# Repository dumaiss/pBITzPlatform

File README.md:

# pBITz Platform

pBITz is the shared hardware platform used by the **Coffee Series** of homebrew computers. It provides the common physical and electrical foundation — backplane, power control, service interfaces, reusable KiCad assets, test hardware, and platform tools — while leaving the personality of each machine to its CPU board and machine-specific peripherals.

The goal is not to define one rigid computer architecture. Instead, pBITz provides a practical common platform on which very different machines can be built: 8-bit, 16-bit, and eventually wider systems can share the same mechanical infrastructure, power distribution, expansion-card format, and platform services without pretending that a Z80, 6309, 68000, 68030, or ARM-class processor has the same bus semantics.

This repository contains the **platform-level** hardware and support material. Machine-specific CPU, video, sound, and operating-system work normally lives in the corresponding Coffee Series repository.

> **Important:** pBITz is a custom parallel expansion bus. The current platform uses DIN 41612-style connectors; it is not PCI Express and is not electrically compatible with PC expansion buses.

## Design philosophy

pBITz deliberately keeps the backplane simple.

The backplane distributes signals, power, clocks, and service connections, but it does not try to impose a universal bus controller or chipset. The CPU board for a particular machine is responsible for turning that machine's native bus into the pBITz signal conventions and for defining how the generic control lines are interpreted.

That leads to a few guiding principles:

- **The backplane is infrastructure, not the computer.** The machine emerges from the CPU board, IO Controller, and installed peripheral cards.
- **Use conventional parallel buses where practical.** Address, data, read/write, interrupt, arbitration, and timing signals remain visible rather than being hidden behind an FPGA SoC.
- **Share mechanics and services without forcing identical CPU semantics.** An 8-bit machine may use only part of the available data/address width; a 16-bit machine can use more of it.
- **Keep platform services separate from machine personality.** Power management, the service SPI bus, removable storage, USB hosting, test interfaces, and reusable CAD assets belong here.
- **Prefer inspectable hardware.** The project is intended to remain understandable with schematics, logic probes, oscilloscopes, PLDs, and ordinary firmware tools.

## Platform overview

At a high level, a pBITz system looks like this:

```text
                        +----------------------+
                        |   Coffee Series      |
                        |     CPU board        |
                        +----------+-----------+
                                   |
          +------------------------+------------------------+
          |                    pBITz bus                    |
          | address / data / control / clocks / power      |
          +-----+------------------+------------------+-----+
                |                  |                  |
          +-----+-----+      +-----+-----+      +-----+-----+
          |  Video    |      |   Sound   |      | Other I/O |
          |   card    |      |   card    |      |   cards   |
          +-----------+      +-----------+      +-----------+
                                   |
                           pBITz backplane
                                   |
                +------------------+------------------+
                |                                     |
          ATX power / PMU                    service / SPI header
                                                      |
                                             +--------+--------+
                                             |   mezzanine     |
                                             | USB host + SD   |
                                             +-----------------+
```

The exact cards and signal meanings depend on the machine being built.

## pBITz bus

The pBITz expansion bus is intentionally broader than any one Coffee Series CPU requires. The current signal set provides room for:

- up to a **24-bit address bus**;
- up to a **16-bit data bus**;
- generic CPU control/status lines (`CTRL_*`) whose meanings are assigned by the CPU implementation;
- chip-select lines;
- multiple clock lines;
- interrupt and bus-control signals;
- a shared platform **SPI/service bus**;
- system reset and power-management signals;
- `+5 V`, `+3.3 V`, and ground distribution.

An individual machine does not need to use every signal. For example, an 8-bit CPU board can use the low data byte and the subset of address/control lines it needs, while a 16-bit machine can make use of the wider path.

The generic control-line approach is deliberate. Signals such as read, write, memory request, I/O request, bus arbitration, wait/ready, interrupt, and byte strobes differ significantly between processor families. The CPU board performs the required mapping rather than forcing every machine through a single artificial protocol.

See [`pBITz_Control_Signals.md`](pBITz_Control_Signals.md) and, more importantly, the current KiCad schematics for the concrete mapping used by a particular hardware revision.

## Backplane

[`pBITzBackplane/`](pBITzBackplane/) contains the main pBITz backplane.

It is primarily a passive bus-distribution board with an always-on power-management island. Its responsibilities include:

- distributing the pBITz address, data, control, clock, and service signals between slots;
- distributing `+5 V`, `+3.3 V`, and ground from an ATX supply;
- providing bus pull-ups where required;
- exposing the platform service interface on an IDC header;
- coordinating ATX power-up and orderly shutdown through the PMU.

The directory contains the KiCad source, fabrication outputs, architecture notes, and revision-specific validation material.

### Power management

The backplane includes an ATtiny-based **PMU** powered from the ATX standby rail. It handles the enclosure power switch and ATX `PS_ON#` / `PWR_OK` sequencing and can coordinate an orderly shutdown with the machine's IO Controller.

PMU firmware lives under [`Code/PMU/`](Code/PMU/).

## Backplane mezzanine

[`pBITzBackplaneMezzanine/`](pBITzBackplaneMezzanine/) contains the platform I/O mezzanine attached through the backplane service connector.

The current design provides:

- a **MAX3421E** SPI USB host controller;
- an **FE1.1** USB hub;
- multiple downstream USB connections;
- an **SD card** operating in SPI mode;
- the necessary buffering, level conversion, power distribution, and card-detect/interrupt paths.

This keeps common storage and USB services out of the CPU-specific logic while still making them available to machines through the platform service interface.

## Platform support hardware

### pBITz Test Card

[`pBITzTestCard/`](pBITzTestCard/) is a work-in-progress platform development and diagnostic card. The current schematic work includes concepts for:

- a console interface;
- external programming support;
- an MCU-based controller;
- USB/JTAG programming and test functions.

This project is currently development hardware rather than a finished production design.

### pBITz Terminal

[`pBITzTerminal/`](pBITzTerminal/) explores a standalone serial terminal suitable for use with pBITz and other retro systems.

The current architecture is based around an HD63C03-family CPU and MC6845-compatible CRTC, with a VGA-style text display, PS/2 keyboard support, serial communications, banked SRAM, programmable character memory, and PLD-based video/bus arbitration.

The terminal is an experimental design and should not be treated as a completed board yet.

## Platform tools and firmware

[`Code/`](Code/) contains code that belongs to the platform rather than to one specific Coffee Series machine.

Current contents include:

- [`Code/PMU/`](Code/PMU/) — ATtiny power-management firmware, including a host-testable state machine;
- [`Code/tools/kicad_nettrace.py`](Code/tools/kicad_nettrace.py) — a KiCad schematic connectivity-analysis helper used during design reviews.

A typical connectivity check is:

```sh
python3 Code/tools/kicad_nettrace.py pBITzBackplane/pBITzBackplane.kicad_sch --check
```

`kicad_nettrace.py` is a review aid, not a replacement for KiCad's own connectivity model. When the helper and KiCad disagree, the **KiCad schematic/netlist is authoritative**.

## Shared KiCad assets

[`99-KiCad-Lib/`](99-KiCad-Lib/) is the shared CAD library used across the platform and Coffee Series projects. It contains:

- custom schematic symbols;
- footprints;
- 3D models;
- pBITz connector definitions;
- reusable parts used by the various machines;
- project artwork and board logos.

Keeping these assets in the platform repository avoids maintaining slightly different copies in every machine repository.

## Datasheets

[`00-Datasheets/`](00-Datasheets/) collects component documentation used while designing the platform and Coffee Series machines. It is organized by broad component class, including:

- analog;
- CPUs and MCUs;
- connectors;
- logic;
- memory;
- oscillators;
- peripherals;
- power components.

The datasheet directory is a working engineering reference, not intended to be a complete historical semiconductor archive.

## Repository layout

| Path | Purpose | Status |
| --- | --- | --- |
| `pBITzBackplane/` | Main backplane, ATX interface, PMU hardware, service bus | Active hardware design |
| `pBITzBackplaneMezzanine/` | Shared USB/SD service mezzanine | Active hardware design |
| `Code/PMU/` | Backplane power-management firmware | Implemented / evolving |
| `Code/tools/` | Platform engineering and KiCad-analysis tools | Active |
| `pBITzTestCard/` | Platform diagnostic/programming card | Work in progress |
| `pBITzTerminal/` | Standalone serial/VGA terminal experiment | Experimental |
| `99-KiCad-Lib/` | Shared KiCad symbols, footprints, and 3D models | Shared infrastructure |
| `00-Datasheets/` | Engineering reference datasheets | Shared infrastructure |
| `pBITz_Control_Signals.md` | Cross-CPU control-signal mapping notes | Design reference |

## Relationship to the Coffee Series

pBITz exists so that the Coffee Series machines can share a physical platform without becoming variants of the same computer.

Examples of machines built or planned around the platform include architectures based on processors such as the Z80, HD6309, 68000/68030, and ARM-class CPUs. Each machine is free to define its own memory architecture, CPU timing, interrupt model, video hardware, sound hardware, firmware, and operating system while reusing the pBITz mechanical and platform infrastructure where it makes sense.

In other words:

> **pBITz provides the chassis and electrical vocabulary; the CPU and peripheral set define the computer.**

## Source of truth and revision notes

This is an actively developed hardware platform. Schematics, PCB layouts, production files, architecture notes, and validation reports do not always change at the same time.

When reviewing a design:

1. treat the current **KiCad schematic and PCB files** as the source of truth for the active hardware revision;
2. use architecture documents to explain intent and operation;
3. check the date/revision of validation reports and fabrication outputs before assuming they describe the current board;
4. regenerate production files after a hardware revision rather than assuming an older BOM/Gerber package remains current.

This is particularly important when a mechanical or connector revision changes without altering the higher-level bus concept.

## Hardware status and validation

Validation reports in this repository document engineering checks performed against particular revisions of the design files. They are useful review records, but they are not certification and do not replace physical bring-up.

Unless explicitly stated otherwise, repository-level validation may include schematic/netlist consistency and selected PCB checks, while powered measurements, signal-integrity characterization, enclosure fit, manufacturing tolerances, and real-hardware testing remain separate activities.

## License

Unless noted otherwise, the hardware and associated source material in this repository are released under the **Solderpad Hardware License v2.1**, with the option described in the license to treat the work under Apache License 2.0.

See [`Licence.md`](Licence.md) for the complete terms.

---

pBITz is an evolving homebrew-computer platform. Expect the schematics to remain understandable, the buses to remain visible, and occasionally a logic analyzer to become part of the debugging process.

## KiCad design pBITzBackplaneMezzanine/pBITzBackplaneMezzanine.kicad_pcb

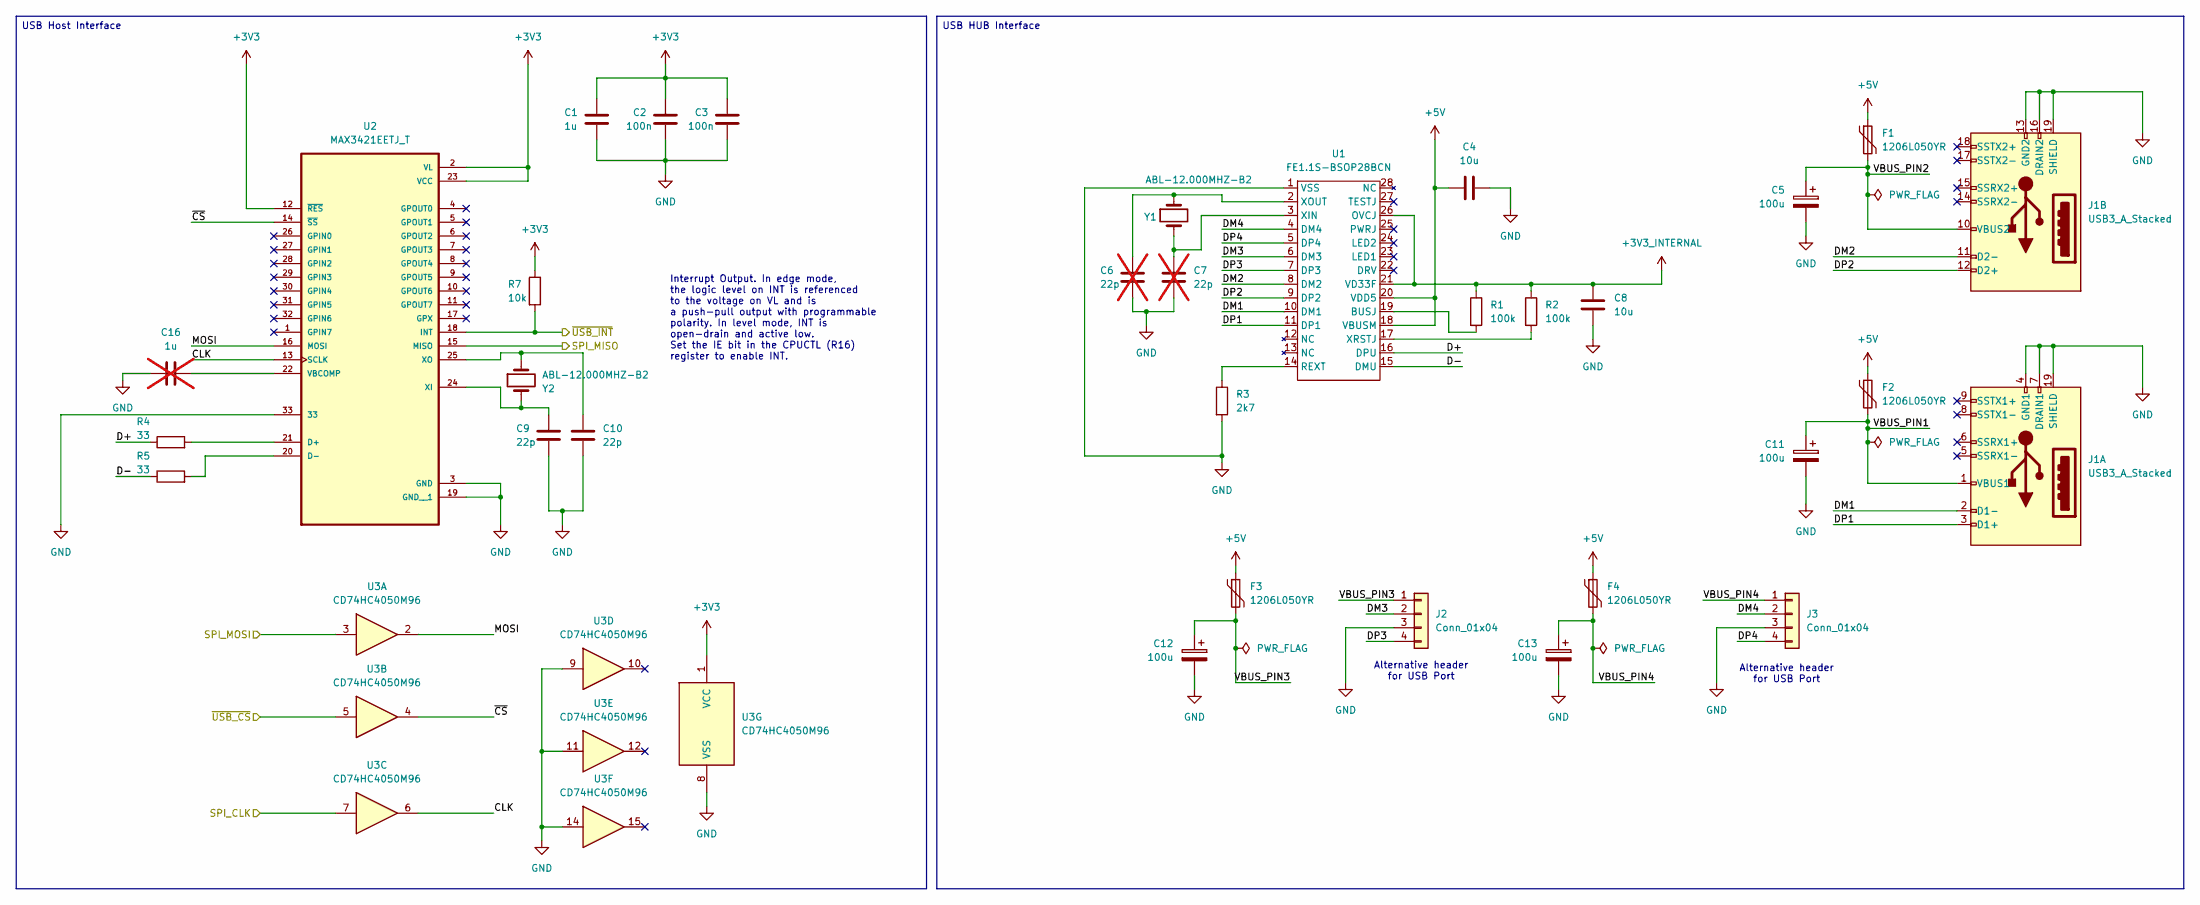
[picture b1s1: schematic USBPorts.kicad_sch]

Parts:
C1: 1u; C_0603_1608Metric; MANUFACTURER_PART_NUMBER C0603C105K4RACTU
C2, C3: 100n; C_0603_1608Metric; MANUFACTURER_PART_NUMBER C0603C104K5RACTU
C4, C8: 10u; C_0603_1608Metric; MANUFACTURER_PART_NUMBER CL10X106MO8NRNC
C5, C11, C12, C13: 100u; CP_Radial_D5.0mm_P2.50mm; MANUFACTURER_PART_NUMBER ECA-1CHG101I
C6, C7: 22p; C_0603_1608Metric; not fitted
C9, C10: 22p; C_0603_1608Metric; MANUFACTURER_PART_NUMBER KGM15ACG1C220KT
C16: 1u; C_0603_1608Metric; MANUFACTURER_PART_NUMBER CL10X106MO8NRNC; not fitted
F1, F2, F3, F4: 1206L050YR; Fuse_1206_3216Metric; MANUFACTURER_PART_NUMBER 1206L050YR
J1: USB3_A_Stacked; USB3_A_Molex_48406-0001_Horizontal_Stacked; MANUFACTURER_PART_NUMBER 0484060001
J2, J3: Conn_01x04; PinHeader_1x04_P2.54mm_Vertical; MANUFACTURER_PART_NUMBER 732-5301-ND
R1, R2: 100k; R_0603_1608Metric; MANUFACTURER_PART_NUMBER RMCF0603FT100K
R3: 2k7; R_0603_1608Metric; MANUFACTURER_PART_NUMBER RC0603JR-072K7L
R4, R5: 33; R_0603_1608Metric; MANUFACTURER_PART_NUMBER RC0603FR-0733RL
R7: 10k; R_0603_1608Metric; MANUFACTURER_PART_NUMBER RC0603FR-0710KL
U1: FE1.1S-BSOP28BCN; SSOP-28_5.3x10.2mm_P0.65mm; MANUFACTURER_PART_NUMBER FE1.1S-BSOP28BCN
U2: MAX3421EETJ_T; QFN50P500X500X80-33N; MANUFACTURER_PART_NUMBER MAX3421EETJ+T
U3: CD74HC4050M96; SOIC-16_3.9x9.9mm_P1.27mm; MANUFACTURER_PART_NUMBER CD74HC4050M96
Y1, Y2: ABL-12.000MHZ-B2; Crystal_HC49-U_Vertical; MANUFACTURER_PART_NUMBER ABL-12.000MHZ-B2

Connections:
+3V3: C1.2, C2.2, C3.2, R7.1, U2.2 (VL), U2.12 (~RES), U2.23 (VCC), U3.1 (VCC); also elsewhere on the board
+3V3_INTERNAL: C8.1, R1.1, R2.1, U1.21 (VD33F), U1.26 (OVCJ)
+5V: C4.1, F1.1, F2.1, F3.1, F4.1, U1.18 (VBUSM), U1.20 (VDD5); also elsewhere on the board
/MezzanineConnector/MISO: U2.15 (MISO); also elsewhere on the board
/MezzanineConnector/MOSI: U3.3; also elsewhere on the board
/MezzanineConnector/SPI_CLK: U3.7; also elsewhere on the board
/MezzanineConnector/SPI_CS0: U3.5; also elsewhere on the board
/MezzanineConnector/~SPI_INT: R7.2, U2.18 (INT); also elsewhere on the board
/USBPorts/CLK: U2.13 (SCLK), U3.6
/USBPorts/D+: R4.1, U1.16 (DPU)
/USBPorts/D-: R5.1, U1.15 (DMU)
/USBPorts/DM1: J1.2 (D1-), U1.10 (DM1)
/USBPorts/DM2: J1.11 (D2-), U1.8 (DM2)
/USBPorts/DM3: J2.2, U1.6 (DM3)
/USBPorts/DM4: J3.2, U1.4 (DM4)
/USBPorts/DP1: J1.3 (D1+), U1.11 (DP1)
/USBPorts/DP2: J1.12 (D2+), U1.9 (DP2)
/USBPorts/DP3: J2.4, U1.7 (DP3)
/USBPorts/DP4: J3.4, U1.5 (DP4)
/USBPorts/MOSI: U2.16 (MOSI), U3.2
/USBPorts/VBUS_PIN1: C11.1, F2.2, J1.1 (VBUS1)
/USBPorts/VBUS_PIN2: C5.1, F1.2, J1.10 (VBUS2)
/USBPorts/VBUS_PIN3: C12.1, F3.2, J2.1
/USBPorts/VBUS_PIN4: C13.1, F4.2, J3.1
/USBPorts/~CS: U2.14 (~SS), U3.4
GND: C1.1, C2.1, C3.1, C4.2, C5.2, C6.1, C7.1, C8.2, C9.1, C10.1, C11.2, C12.2, C13.2, C16.1, J1.4 (GND1), J1.7 (DRAIN1), J1.13 (GND2), J1.16 (DRAIN2), J1.19 (SHIELD), J2.3, J3.3, R3.2, U1.1 (VSS), U2.3 (GND), U2.19 (GND__1), U2.33, U3.8 (VSS), U3.9, U3.11, U3.14; also elsewhere on the board
unnamed: R1.2, U1.19 (BUSJ)
unnamed: R3.1, U1.14 (REXT)
unnamed: C7.2, U1.3 (XIN), Y1.2
unnamed: C6.2, U1.2 (XOUT), Y1.1
unnamed: R2.2, U1.17 (XRSTJ)
unnamed: R4.2, U2.21 (D+)
unnamed: R5.2, U2.20 (D-)
unnamed: C16.2, U2.22 (VBCOMP)
unnamed: C9.2, U2.24 (XI), Y2.2
unnamed: C10.2, U2.25 (XO), Y2.1

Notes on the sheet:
Interrupt Output. In edge mode, the logic level on INT is referenced to the voltage on VL and is a push-pull output with programmable polarity. In level mode, INT is open-drain and active low. Set the IE bit in the CPUCTL (R16) register to enable INT.
Alternative header for USB Port
USB HUB Interface
USB Host Interface

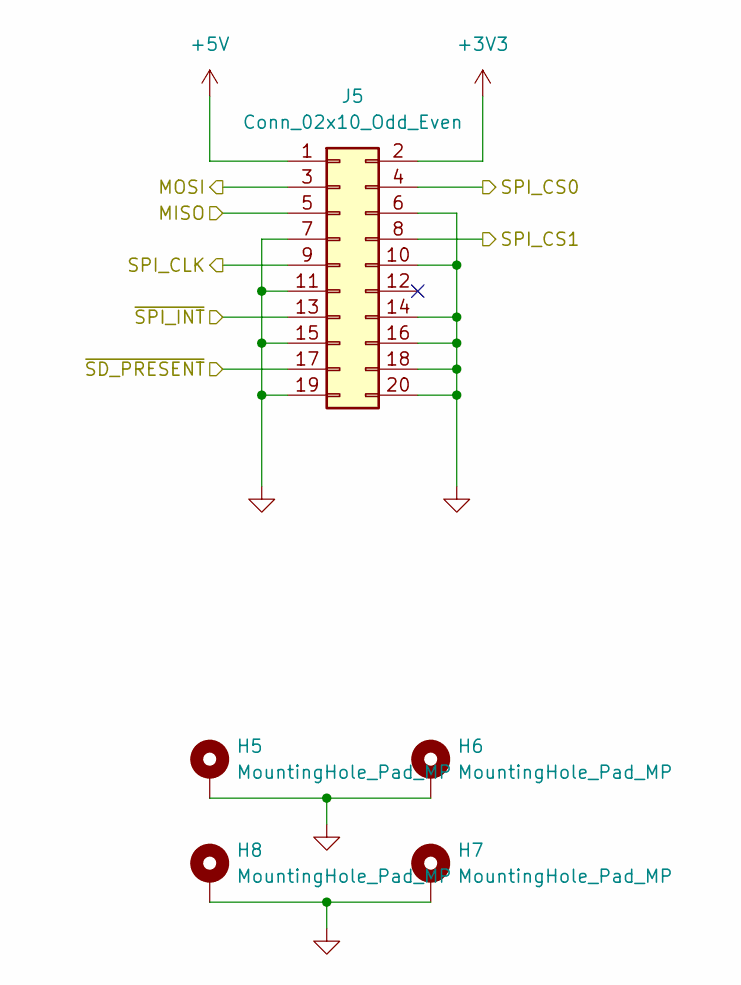
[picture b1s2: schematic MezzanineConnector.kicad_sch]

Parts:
H5, H6, H7, H8: MountingHole_Pad_MP; MountingHole_3.2mm_M3_Pad_TopBottom
J5: Conn_02x10_Odd_Even; IDC-Header_2x10_P2.54mm_Vertical; MANUFACTURER_PART_NUMBER SBH11-PBPC-D10-ST-BK

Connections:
+3V3: J5.2; also elsewhere on the board
+5V: J5.1; also elsewhere on the board
/MezzanineConnector/MISO: J5.5; also elsewhere on the board
/MezzanineConnector/MOSI: J5.3; also elsewhere on the board
/MezzanineConnector/SPI_CLK: J5.9; also elsewhere on the board
/MezzanineConnector/SPI_CS0: J5.4; also elsewhere on the board
/MezzanineConnector/SPI_CS1: J5.8; also elsewhere on the board
/MezzanineConnector/~SD_PRESENT: J5.17; also elsewhere on the board
/MezzanineConnector/~SPI_INT: J5.13; also elsewhere on the board
GND: H5.MP, H6.MP, H7.MP, H8.MP, J5.6, J5.7, J5.10, J5.11, J5.14, J5.15, J5.16, J5.18, J5.19, J5.20; also elsewhere on the board

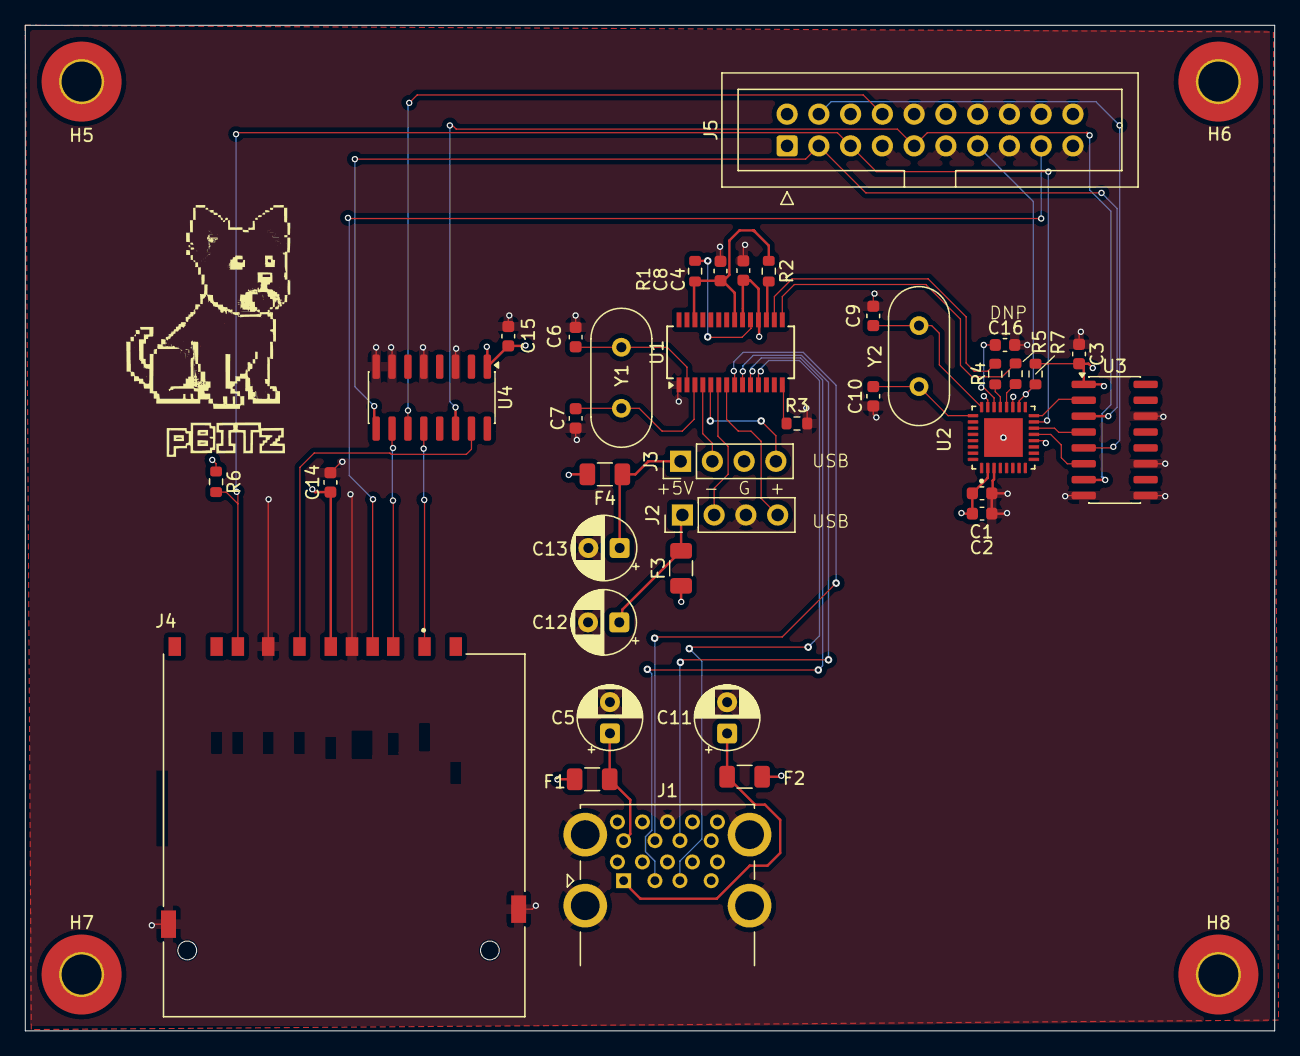
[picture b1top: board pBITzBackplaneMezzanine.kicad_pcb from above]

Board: 4 copper layers, 99.9 x 80.4 mm, 42 parts (0 on the bottom side), 41 nets.

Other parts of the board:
C14, C15: 100n; C_0603_1608Metric
J4: 10067847-001RLF; AMPHENOL_10067847-001RLF
R6: 10k; R_0603_1608Metric
U4: CD74HC4050M96; SOIC-16_3.9x9.9mm_P1.27mm

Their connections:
+3V3: C14.1, C15.1, J4.4 (VDD), R6.1, U4.1 (VCC); also elsewhere on the board
/MezzanineConnector/MISO: J4.7 (DAT0), R6.2; also elsewhere on the board
/MezzanineConnector/MOSI: U4.9; also elsewhere on the board
/MezzanineConnector/SPI_CLK: U4.14; also elsewhere on the board
/MezzanineConnector/SPI_CS1: U4.11; also elsewhere on the board
/MezzanineConnector/~SD_PRESENT: J4.CD; also elsewhere on the board
/SD_Card/CLK: J4.5 (CLK), U4.15
/SD_Card/MOSI: J4.2 (CMD), U4.10
/SD_Card/~CS: J4.1 (DAT3/CD), U4.12
GND: C14.2, C15.2, J4.3 (VSS), J4.6 (VSS__1), J4.G1 (GND), J4.G2 (GND__1), U4.3, U4.5, U4.7, U4.8 (VSS); also elsewhere on the board

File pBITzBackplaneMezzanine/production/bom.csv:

Designator,Footprint,Quantity,Value,LCSC Part #
"C1, C16",0603,2,1u,
"C10, C6, C7, C9",0603,4,22p,
"C11, C12, C13, C5",CP_Radial_D5.0mm_P2.50mm,4,100u,
"C14, C15, C2, C3",0603,4,100n,
"C4, C8",0603,2,10u,
"F1, F2, F3, F4",1206,4,1206L050YR,
J1,USB3_A_Molex_48406-0001_Horizontal_Stacked,1,USB3_A_Stacked,
"J2, J3",PinHeader_1x04_P2.54mm_Vertical,2,Conn_01x04,
J4,AMPHENOL_10067847-001RLF,1,10067847-001RLF,
J5,IDC-Header_2x10_P2.54mm_Vertical,1,Conn_02x10_Odd_Even,
"R1, R2",0603,2,100k,
R3,0603,1,2k7,
"R4, R5",0603,2,33,
"R6, R7",0603,2,10k,
U1,SSOP-28_5.3x10.2mm_P0.65mm,1,FE1.1S-BSOP28BCN,
U2,QFN50P500X500X80-33N,1,MAX3421EETJ_T,
"U3, U4",SOIC-16_3.9x9.9mm_P1.27mm,2,CD74HC4050M96,
"Y1, Y2",Crystal_HC49-U_Vertical,2,ABL-12.000MHZ-B2,

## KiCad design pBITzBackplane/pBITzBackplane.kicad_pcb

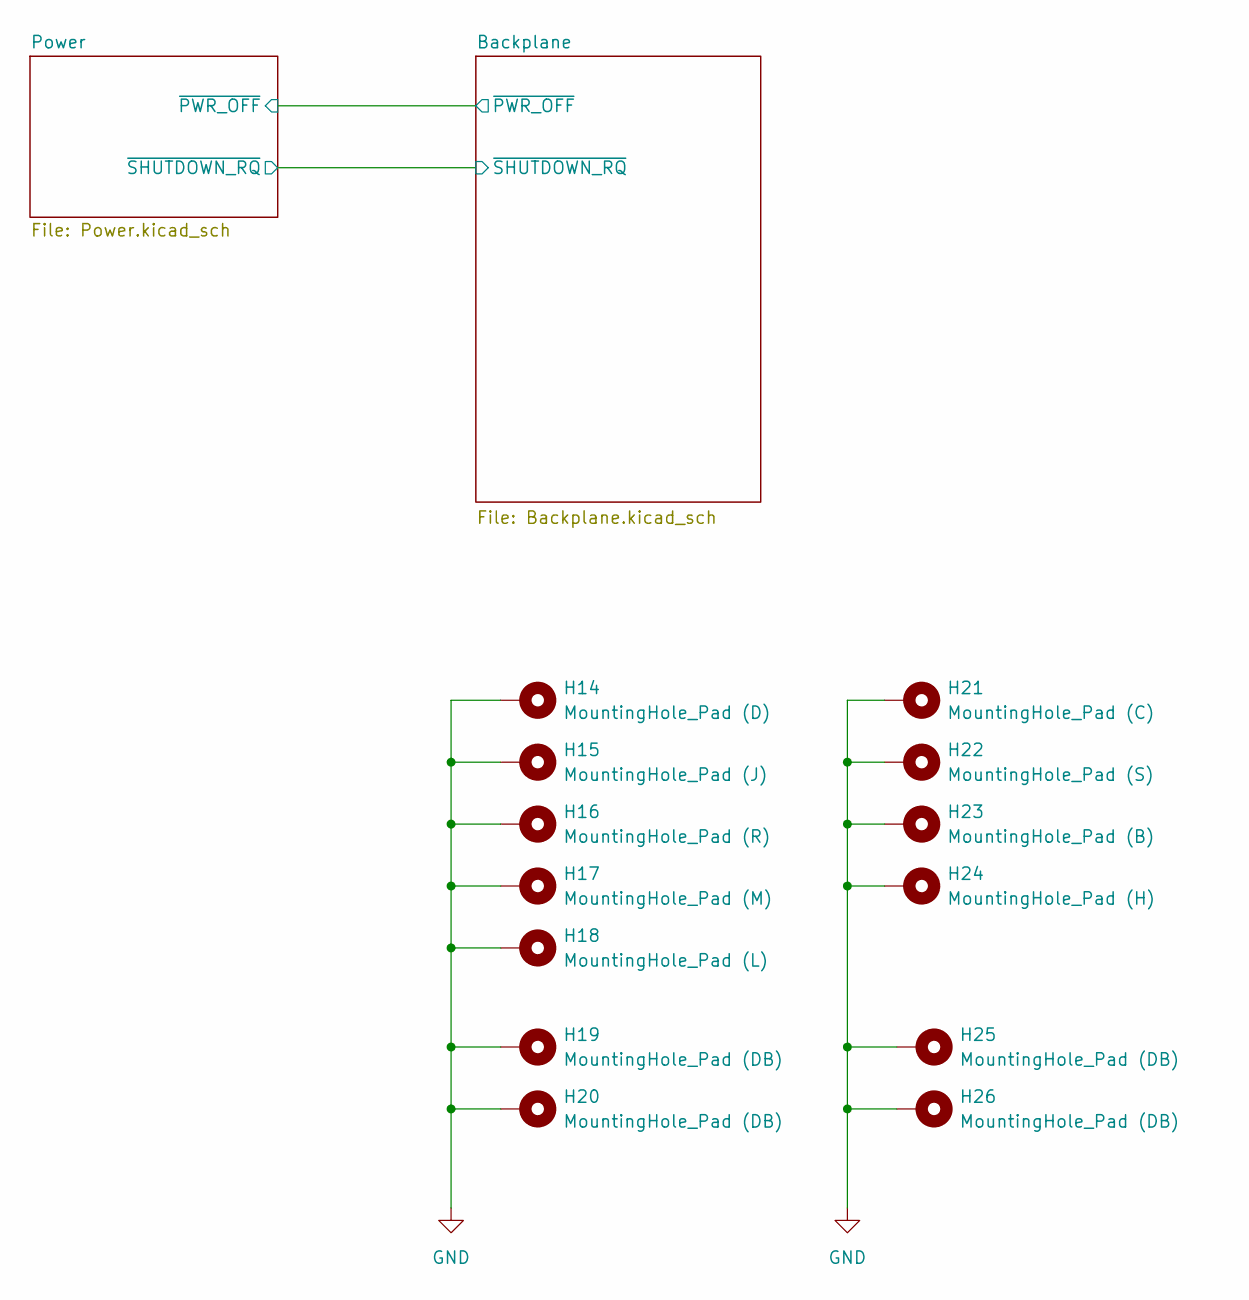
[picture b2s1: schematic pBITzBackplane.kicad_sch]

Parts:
H14: MountingHole_Pad (D); MountingHole_3.5mm_Pad_TopBottom
H15: MountingHole_Pad (J); MountingHole_3.5mm_Pad_TopBottom
H16: MountingHole_Pad (R); MountingHole_3.5mm_Pad_TopBottom
H17: MountingHole_Pad (M); MountingHole_3.5mm_Pad_TopBottom
H18: MountingHole_Pad (L); MountingHole_3.5mm_Pad_TopBottom
H19, H20, H25, H26: MountingHole_Pad (DB); MountingHole_3.5mm_Pad_TopBottom
H21: MountingHole_Pad (C); MountingHole_3.5mm_Pad_TopBottom
H22: MountingHole_Pad (S); MountingHole_3.5mm_Pad_TopBottom
H23: MountingHole_Pad (B); MountingHole_3.5mm_Pad_TopBottom
H24: MountingHole_Pad (H); MountingHole_3.5mm_Pad_TopBottom

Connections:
GND: H14.1 (1_1), H15.1 (1_1), H16.1 (1_1), H17.1 (1_1), H18.1 (1_1), H19.1 (1_1), H20.1 (1_1), H21.1 (1_1), H22.1 (1_1), H23.1 (1_1), H24.1 (1_1), H25.1 (1_1), H26.1 (1_1); also elsewhere on the board

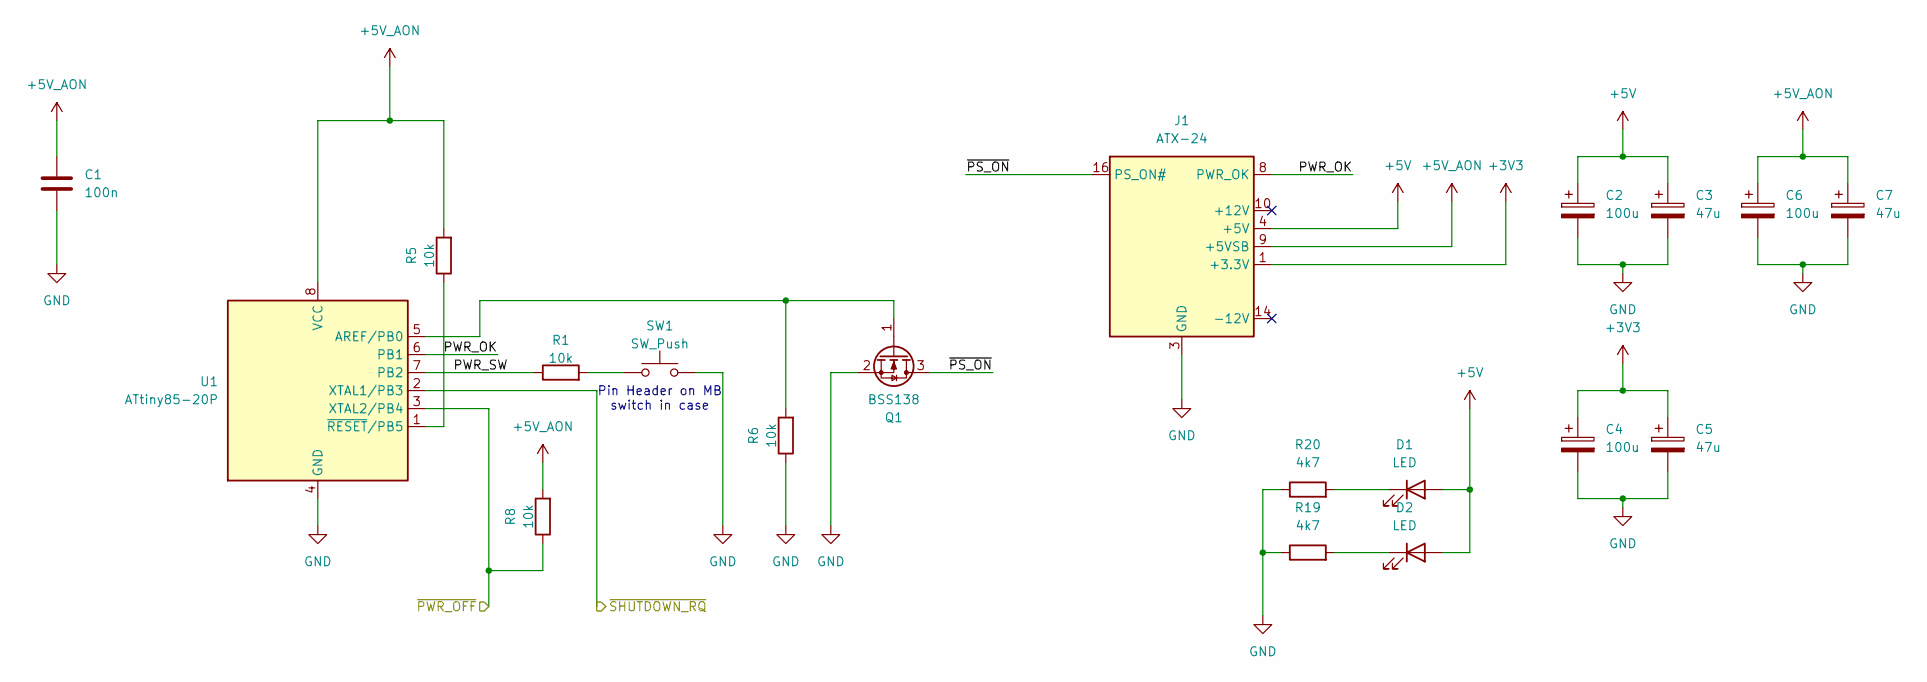
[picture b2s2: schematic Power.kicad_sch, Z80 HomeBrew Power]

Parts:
C1: 100n; C_1206_3216Metric_Pad1.33x1.80mm_HandSolder; MANUFACTURER_PART_NUMBER C1206C104K3RACTU
C2, C4, C6: 100u; CP_Radial_D5.0mm_P2.00mm; MANUFACTURER_PART_NUMBER 25YXJ100MTA5X11
C3, C5, C7: 47u; CP_Radial_D5.0mm_P2.00mm; MANUFACTURER_PART_NUMBER 25YXJ47MTA5X11
D1: LED; LED_D5.0mm
D2: LED; PinHeader_2x01_P2.54mm_Vertical
J1: ATX-24; MOLEX_39281243; MANUFACTURER_PART_NUMBER 0039281243
Q1: BSS138; SOT-23; MANUFACTURER_PART_NUMBER BSS138
R1, R5, R6, R8: 10k; R_1206_3216Metric_Pad1.30x1.75mm_HandSolder; MANUFACTURER_PART_NUMBER RC1206FR-0710KL
R19, R20: 4k7; R_1206_3216Metric_Pad1.30x1.75mm_HandSolder; MANUFACTURER_PART_NUMBER RC1206FR-074K7L
SW1: SW_Push; PinHeader_1x02_P2.54mm_Vertical
U1: ATtiny85-20P; DIP-8_W7.62mm; MANUFACTURER_PART_NUMBER A 08-LC-TT

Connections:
+3V3: C4.1, C5.1, J1.1 (+3.3V), J1.2 (+3.3V), J1.12 (+3.3V), J1.13 (+3.3V); also elsewhere on the board
+5V: C2.1, C3.1, D1.2 (A), D2.2 (A), J1.4 (+5V), J1.6 (+5V), J1.21 (+5V), J1.22 (+5V), J1.23 (+5V); also elsewhere on the board
+5V_AON: C1.1, C6.1, C7.1, J1.9 (+5VSB), R5.2, R8.2, U1.8 (VCC)
/Backplane/~PWR_OFF: R8.1, U1.3 (XTAL2/PB4); also elsewhere on the board
/Backplane/~SHUTDOWN_RQ: U1.2 (XTAL1/PB3); also elsewhere on the board
/Power/PWR_OK: J1.8 (PWR_OK), U1.6 (PB1)
/Power/PWR_SW: R1.1, U1.7 (PB2)
/Power/~PS_ON: J1.16 (PS_ON#), Q1.3 (D)
GND: C1.2, C2.2, C3.2, C4.2, C5.2, C6.2, C7.2, J1.3 (GND), J1.5 (GND), J1.7 (GND), J1.15 (GND), J1.17 (GND), J1.18 (GND), J1.19 (GND), J1.24 (GND), Q1.2 (S), R6.1, R19.1, R20.1, SW1.2, U1.4 (GND); also elsewhere on the board
unnamed: D1.1 (K), R20.2
unnamed: D2.1 (K), R19.2
unnamed: Q1.1 (G), R6.2, U1.5 (AREF/PB0)
unnamed: R1.2, SW1.1
unnamed: R5.1, U1.1 (~RESET/PB5)

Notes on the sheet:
Pin Header on MB switch in case
